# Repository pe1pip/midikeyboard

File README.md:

# Midi Keyboard

[[_TOC_]]

## Introduction

Copyright 2026 Remco Post

[License AGPL](./LICENSE.md)

## de-mux

The software is designed to use a one-of-eight demux like the 74hc238 to scan a keyboard. With 8 lines this could
be up to 5 octave (and a bit).

## Stops

The stops are not multiplexed. The software supports 8 stops. The trick is that each of the stops cycles through
6 options:

- off
- on (no shift)
- on (1 up)
- on (1 down)
- on (2 up)
- on (2 down)

On a stop change the software first sends 'key off', unless the stop is currently off, followed by the key on that
corresponds with the stop and shift. To facilitate that, each stop actually uses 5 values: 2, 3, 4, 5 and 6 with
an offset in mutiples of 8 for each stop.

### Stop state

The stop state is stored in an array with a value that corresponds to one of the 6 possible options. The state of the
stop buttons is also stored. On a LOW to HIGH transition the stop state is updated and the new value is transmitted.

## MIDI channels

Configurable in code, but defined as:

0: stops
1: keys

## Key state

The (previous) key state is stored in an array. If the value has changed the new value is send over the serial line immediately.

## Keyboard

The keyboard is a simple matrix, 8 input lines, diodes to each key contact and then 8 lines. The current flows from 'Keys in group' to 'Group'.
The (previous) key state is stored in an array. If the value has changed the new value is send over the serial line
immediately.

### Groups

| keys | pin | giga pin |
|------|-----|----------|
| 1-8  | 16  | 53       |
| 9-16 | 1   | 52       |
| 17-24| 15  | 51       |
| 25-32| 2   | 50       |
| 33-40| 14  | 49       |
| 41-48| 3   | 48       |
| 49-56| 13  | 47       |
| 57-61| 4   | 46       |

### Keys in group

| key | pin | giga pin |
|-----|-----|----------|
| 1   | 10  | 41       |
| 2   | 5   | 44       |
| 3   | 6   | 42       |
| 4   | 12  | 45       |
| 5   | 11  | 43       |
| 6   | 9   | 39       |
| 7   | 8   | 38       |
| 8   | 7   | 40       |

### Scanning the keyboard

The 'group' lines are pulled up via the internal pullup resister. If a key is depressed and the 'Keys in group'
line is `LOW`, then the 'group' line goes `LOW`. So, normally all 'Key in group' lines are high. Then one by one
each is set to `LOW`, and all 'Group' lines are read to see which of the keys are depressed; those will read `LOW`.
After a key has changed, we don't read the new state for some time `DEBOUNCE` to debounce the keypresses and releases.

## Calcant

Calcant is a special switch, it basically turns off the blower. To draw attention to the blower being off,
the LED will blink. This switch is debounced in the same manner as as the keyboard.

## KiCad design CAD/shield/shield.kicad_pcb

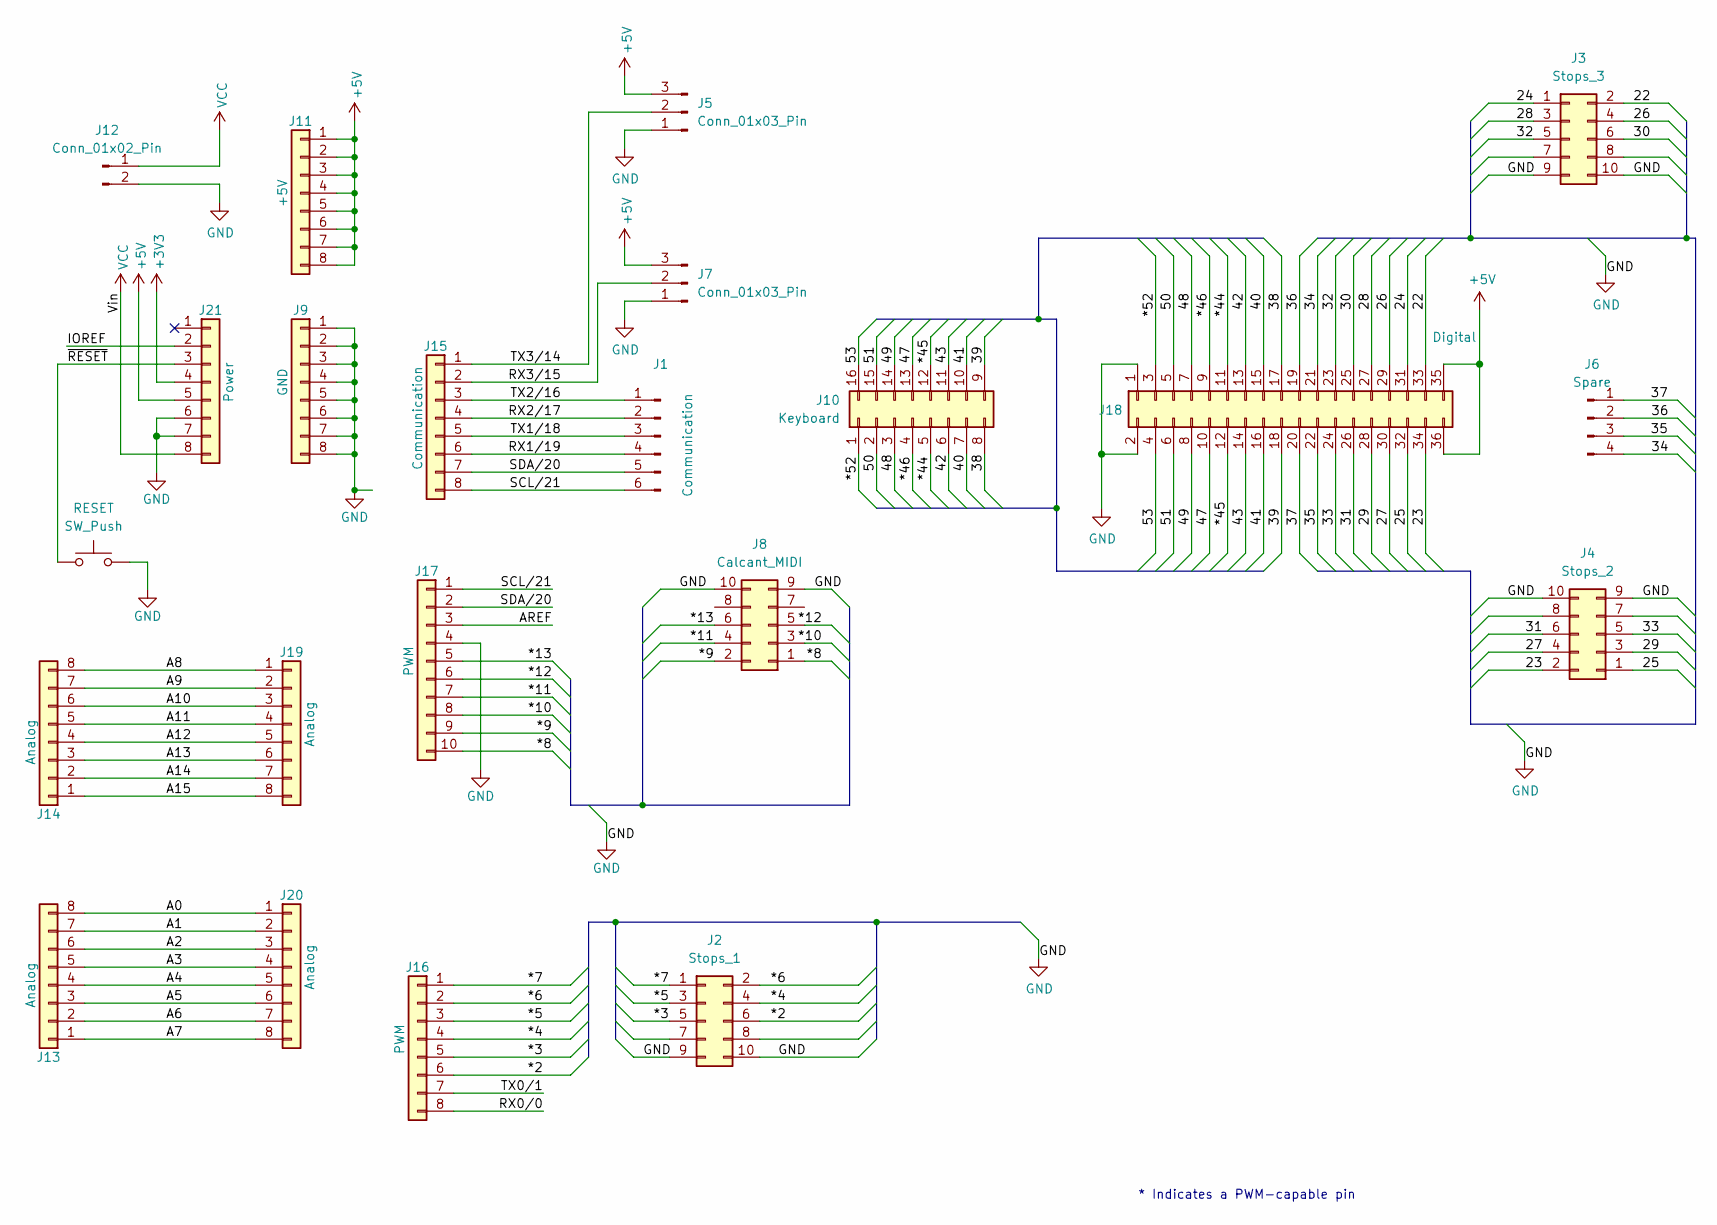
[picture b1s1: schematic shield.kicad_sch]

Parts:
J1: Communication; PinHeader_1x06_P2.54mm_Vertical
J2: Stops_1; IDC-Header_2x05_P2.54mm_Latch_Vertical
J3: Stops_3; IDC-Header_2x05_P2.54mm_Latch_Vertical
J4: Stops_2; IDC-Header_2x05_P2.54mm_Latch_Vertical
J5, J7: Conn_01x03_Pin; PinHeader_1x03_P2.54mm_Vertical
J6: Spare; PinHeader_1x04_P2.54mm_Vertical
J8: Calcant_MIDI; IDC-Header_2x05_P2.54mm_Latch_Vertical
J9: GND; PinHeader_1x08_P2.54mm_Vertical
J10: Keyboard; DIP-16_W7.62mm_Socket
J11: +5V; PinHeader_1x08_P2.54mm_Vertical
J12: Conn_01x02_Pin; PinHeader_1x02_P2.54mm_Vertical
J13, J14, J19, J20: Analog; PinHeader_1x08_P2.54mm_Vertical
J15: Communication; PinHeader_1x08_P2.54mm_Vertical
J16: PWM; PinHeader_1x08_P2.54mm_Vertical
J17: PWM; PinHeader_1x10_P2.54mm_Vertical
J18: Digital; PinHeader_2x18_P2.54mm_Vertical
J21: Power; PinHeader_1x08_P2.54mm_Vertical
RESET: SW_Push; SW_Push_1P1T_NO_CK_KMR2

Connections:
+3V3: J21.4
+5V: J5.3, J7.3, J11.1, J11.2, J11.3, J11.4, J11.5, J11.6, J11.7, J11.8, J18.35, J18.36, J21.5
/22: J3.2, J18.33
/23: J4.2, J18.34
/24: J3.1, J18.31
/25: J4.1, J18.32
/26: J3.4, J18.29
/27: J4.4, J18.30
/28: J3.3, J18.27
/29: J4.3, J18.28
/30: J3.6, J18.25
/31: J4.6, J18.26
/32: J3.5, J18.23
/33: J4.5, J18.24
/34: J6.4, J18.21
/35: J6.3, J18.22
/36: J6.2, J18.19
/37: J6.1, J18.20
/38: J10.8, J18.17
/39: J10.9, J18.18
/40: J10.7, J18.15
/41: J10.10, J18.16
/42: J10.6, J18.13
/43: J10.11, J18.14
/47: J10.13, J18.10
/48: J10.3, J18.7
/49: J10.14, J18.8
/50: J10.2, J18.5
/51: J10.15, J18.6
/53: J10.16, J18.4
/*2: J2.6, J16.6
/*3: J2.5, J16.5
/*4: J2.4, J16.4
/*5: J2.3, J16.3
/*6: J2.2, J16.2
/*7: J2.1, J16.1
/*8: J8.1, J17.10
/*9: J8.2, J17.9
/*10: J8.3, J17.8
/*11: J8.4, J17.7
/*12: J8.5, J17.6
/*13: J8.6, J17.5
/*44: J10.5, J18.11
/*45: J10.12, J18.12
/*46: J10.4, J18.9
/*52: J10.1, J18.3
/A0: J13.8, J20.1
/A1: J13.7, J20.2
/A2: J13.6, J20.3
/A3: J13.5, J20.4
/A4: J13.4, J20.5
/A5: J13.3, J20.6
/A6: J13.2, J20.7
/A7: J13.1, J20.8
/A8: J14.8, J19.1
/A9: J14.7, J19.2
/A10: J14.6, J19.3
/A11: J14.5, J19.4
/A12: J14.4, J19.5
/A13: J14.3, J19.6
/A14: J14.2, J19.7
/A15: J14.1, J19.8
/AREF: J17.3
/IOREF: J21.2
/RX0/0: J16.8
/RX1/19: J1.4, J15.6
/RX2/17: J1.2, J15.4
/RX3/15: J7.2, J15.2
/SCL/21: J1.6, J15.8, J17.1
/SDA/20: J1.5, J15.7, J17.2
/TX0/1: J16.7
/TX1/18: J1.3, J15.5
/TX2/16: J1.1, J15.3
/TX3/14: J5.2, J15.1
/~RESET: J21.3, RESET.1
GND: J2.9, J2.10, J3.9, J3.10, J4.9, J4.10, J5.1, J7.1, J8.9, J8.10, J9.1, J9.2, J9.3, J9.4, J9.5, J9.6, J9.7, J9.8, J12.2, J17.4, J18.1, J18.2, J21.6, J21.7, RESET.2
VCC: J12.1, J21.8

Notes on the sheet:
* Indicates a PWM-capable pin

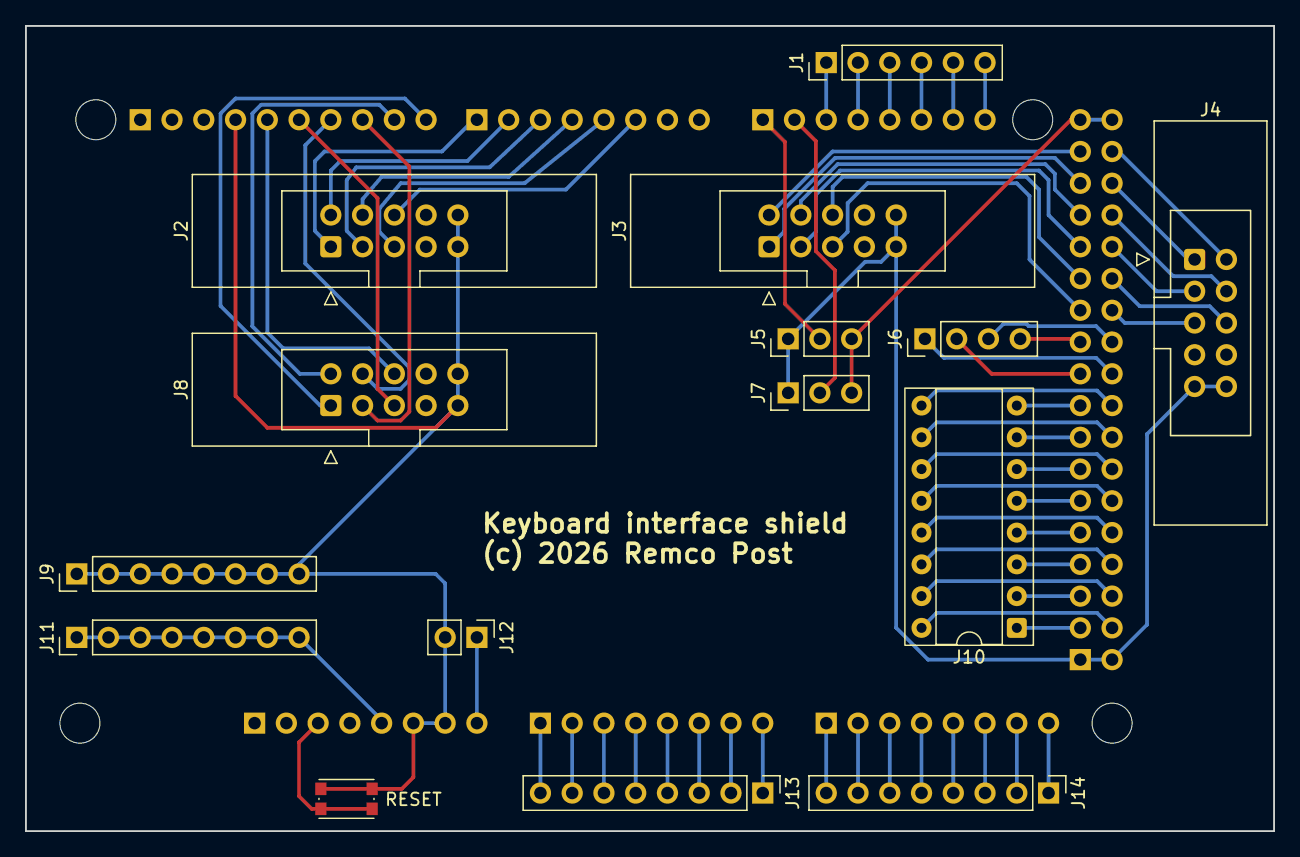
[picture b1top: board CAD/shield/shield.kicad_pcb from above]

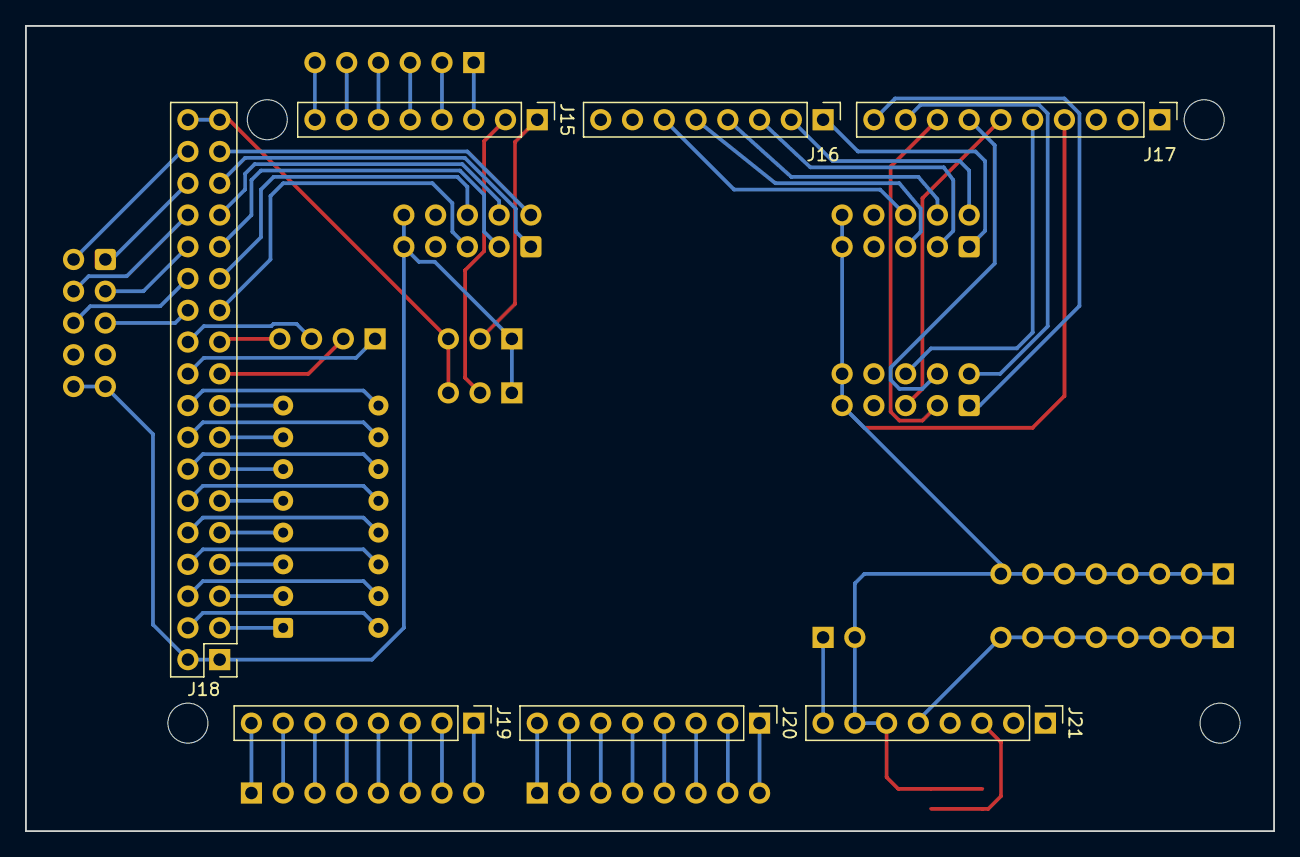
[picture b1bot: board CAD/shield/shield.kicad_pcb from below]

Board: 2 copper layers, 99.8 x 64.4 mm, 26 parts (7 on the bottom side), 72 nets.

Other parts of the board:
MH1, MH2, MH3, MH4: MountingHole_3.2mm

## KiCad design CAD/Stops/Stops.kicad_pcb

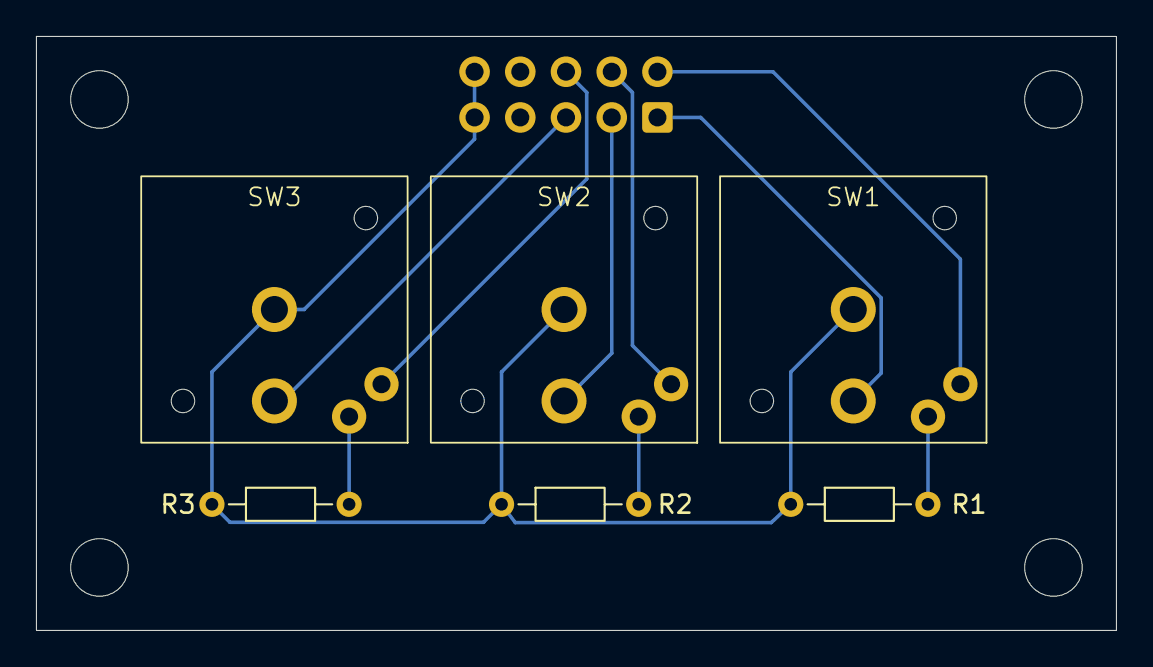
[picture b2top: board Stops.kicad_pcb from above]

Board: 2 copper layers, 60.0 x 33.0 mm, 11 parts (1 on the bottom side), 10 nets.

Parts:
H1, H2, H3, H4: MountingHole; MountingHole_3.2mm_M3
J1: Conn_01x08_Socket; IDC-Header_2x05_P2.54mm_Latch_Horizontal
R1, R2, R3: 270; R_Axial_DIN0204_L3.6mm_D1.6mm_P7.62mm_Horizontal
SW1, SW2, SW3: SW_Push_LED; Marquardt_6425.4111

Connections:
/L1: J1.2, SW1.4 (A)
/L2: J1.4, SW2.4 (A)
/L3: J1.6, SW3.4 (A)
/SW1: J1.1, SW1.2
/SW2: J1.3, SW2.2
/SW3: J1.5, SW3.2
GND: J1.9, J1.10, R1.1, R2.1, R3.1, SW1.1, SW2.1, SW3.1
unnamed: R1.2, SW1.3 (K)
unnamed: R2.2, SW2.3 (K)
unnamed: R3.2, SW3.3 (K)

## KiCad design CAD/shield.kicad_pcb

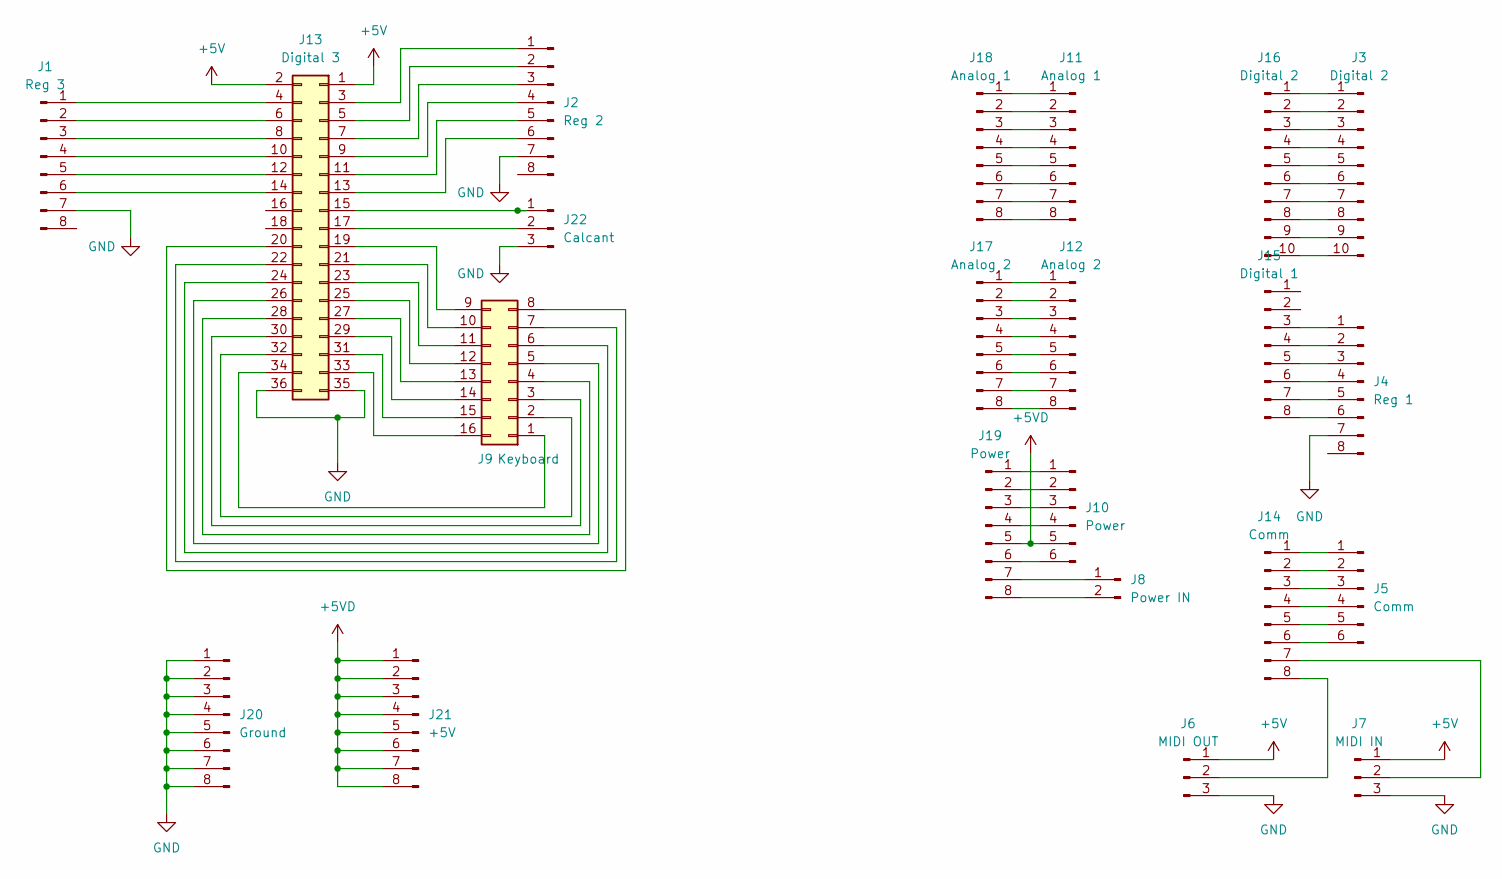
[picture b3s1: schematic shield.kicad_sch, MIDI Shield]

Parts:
J1: Reg 3; PinHeader_1x08_P2.54mm_Vertical
J2: Reg 2; PinHeader_1x08_P2.54mm_Vertical
J3, J16: Digital 2; PinHeader_1x10_P2.54mm_Vertical
J4: Reg 1; PinHeader_1x08_P2.54mm_Vertical
J5: Comm; PinHeader_1x06_P2.54mm_Vertical
J6: MIDI OUT; PinHeader_1x03_P2.54mm_Vertical
J7: MIDI IN; PinHeader_1x03_P2.54mm_Vertical
J8: Power IN; PinHeader_1x02_P2.54mm_Vertical
J9: Keyboard; DIP-16_W7.62mm_Socket
J10: Power; PinHeader_1x06_P2.54mm_Vertical
J11, J18: Analog 1; PinHeader_1x08_P2.54mm_Vertical
J12, J17: Analog 2; PinHeader_1x08_P2.54mm_Vertical
J13: Digital 3; PinHeader_2x18_P2.54mm_Vertical
J14: Comm; PinHeader_1x08_P2.54mm_Vertical
J15: Digital 1; PinHeader_1x08_P2.54mm_Vertical
J19: Power; PinHeader_1x08_P2.54mm_Vertical
J20: Ground; PinHeader_1x08_P2.54mm_Vertical
J21: +5V; PinHeader_1x08_P2.54mm_Vertical
J22: Calcant; PinHeader_1x03_P2.54mm_Vertical

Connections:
+5V: J6.1, J7.1, J13.1, J13.2
+5VD: J10.5, J19.5, J21.1, J21.2, J21.3, J21.4, J21.5, J21.6, J21.7, J21.8
GND: J1.7, J2.7, J4.7, J6.3, J7.3, J13.35, J13.36, J20.1, J20.2, J20.3, J20.4, J20.5, J20.6, J20.7, J20.8, J22.3
unnamed: J1.1, J13.4
unnamed: J1.2, J13.6
unnamed: J1.3, J13.8
unnamed: J1.4, J13.10
unnamed: J1.5, J13.12
unnamed: J1.6, J13.14
unnamed: J10.1, J19.1
unnamed: J10.2, J19.2
unnamed: J10.3, J19.3
unnamed: J10.4, J19.4
unnamed: J10.6, J19.6
unnamed: J11.1, J18.1
unnamed: J11.2, J18.2
unnamed: J11.3, J18.3
unnamed: J11.4, J18.4
unnamed: J11.5, J18.5
unnamed: J11.6, J18.6
unnamed: J11.7, J18.7
unnamed: J11.8, J18.8
unnamed: J12.1, J17.1
unnamed: J12.2, J17.2
unnamed: J12.3, J17.3
unnamed: J12.4, J17.4
unnamed: J12.5, J17.5
unnamed: J12.6, J17.6
unnamed: J12.7, J17.7
unnamed: J12.8, J17.8
unnamed: J2.1, J13.3
unnamed: J2.2, J13.5
unnamed: J2.3, J13.7
unnamed: J2.4, J13.9
unnamed: J2.5, J13.11
unnamed: J2.6, J13.13
unnamed: J13.15, J22.1
unnamed: J13.17, J22.2
unnamed: J9.9, J13.19
unnamed: J9.8, J13.20
unnamed: J9.10, J13.21
unnamed: J9.7, J13.22
unnamed: J9.11, J13.23
unnamed: J9.6, J13.24
unnamed: J9.12, J13.25
unnamed: J9.5, J13.26
unnamed: J9.13, J13.27
unnamed: J9.4, J13.28
unnamed: J9.14, J13.29
unnamed: J9.3, J13.30
unnamed: J9.15, J13.31
unnamed: J9.2, J13.32
unnamed: J9.16, J13.33
unnamed: J9.1, J13.34
unnamed: J5.1, J14.1
unnamed: J5.2, J14.2
unnamed: J5.3, J14.3
unnamed: J5.4, J14.4
unnamed: J5.5, J14.5
unnamed: J5.6, J14.6
unnamed: J7.2, J14.7
unnamed: J6.2, J14.8
unnamed: J4.1, J15.3
unnamed: J4.2, J15.4
unnamed: J4.3, J15.5
unnamed: J4.4, J15.6
unnamed: J4.5, J15.7
unnamed: J4.6, J15.8
unnamed: J3.1, J16.1
unnamed: J3.2, J16.2
unnamed: J3.3, J16.3
unnamed: J3.4, J16.4
unnamed: J3.5, J16.5
unnamed: J3.6, J16.6
unnamed: J3.7, J16.7
unnamed: J3.8, J16.8
unnamed: J3.9, J16.9
unnamed: J3.10, J16.10
unnamed: J8.1, J19.7
unnamed: J8.2, J19.8

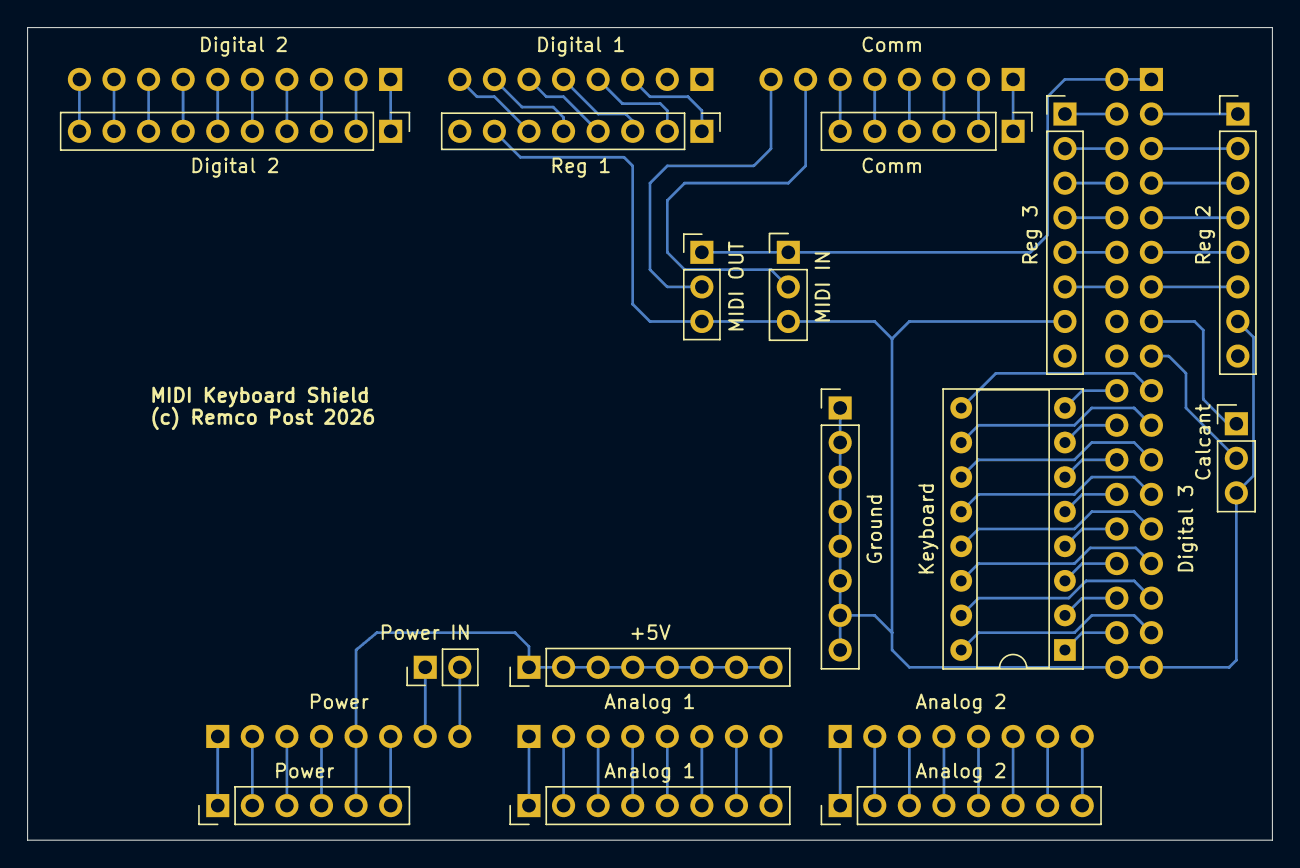
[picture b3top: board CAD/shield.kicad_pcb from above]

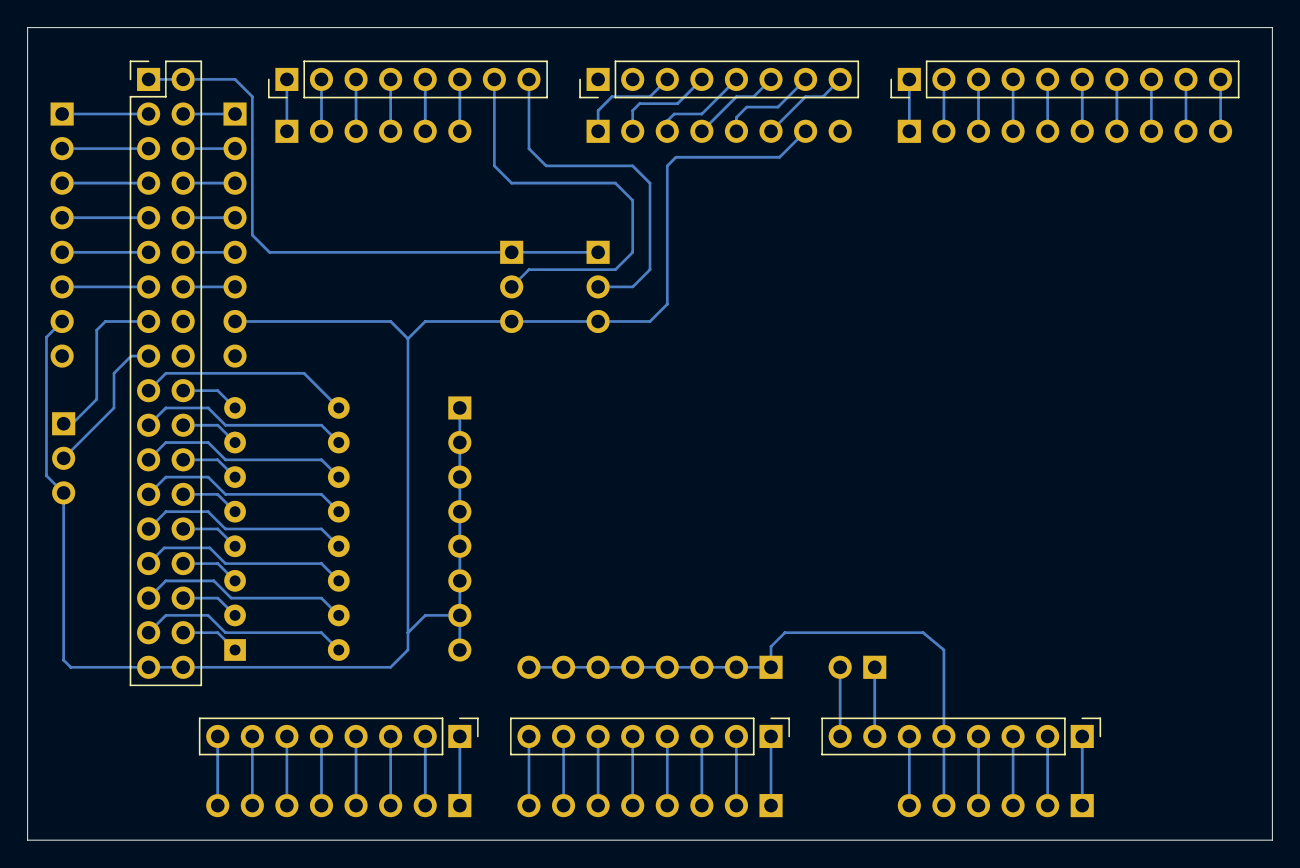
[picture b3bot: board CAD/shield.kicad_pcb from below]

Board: 2 copper layers, 91.4 x 59.7 mm, 22 parts (7 on the bottom side), 80 nets.

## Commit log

2026-05-15 initial
2026-05-15 readme
2026-05-15 done? no docs yet
2026-05-16 var names to camelCase docs
2026-05-17 add console log
2026-05-18 fix pin assignment
2026-05-24 giga
2026-05-27 Add license Add code to handle keypresses on the stops
2026-05-27 Add license
2026-06-01 Added PCB
2026-06-01 updated schematic
2026-06-01 split into modules
2026-06-02 Adjusted for arduino Due board
2026-06-02 betetr param name
2026-06-03 Stop switch PCB
2026-06-03 save
2026-06-04 namespaces
2026-06-04 not DUE but Mega
2026-06-07 improved footprint
2026-06-09 fix pins
2026-06-09 moved from stop ISR to polling, Mega has too few interrupts
2026-06-10 merging
2026-06-10 small improvements
2026-06-13 redo CAD
2026-06-13 improved button/led handling
2026-06-15 introduce wifiMidi
2026-06-15 bugfix
2026-06-15 bugfix on keyboard scan
2026-06-16 more bugfix

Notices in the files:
CAD/shield.kicad_pcb:
GPL V3.0 or later
CAD/shield/shield.kicad_pcb:
(c) 2026 Remco Post
